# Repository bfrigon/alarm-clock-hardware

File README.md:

alarm-clock
===========

Project page at http://www.bfrigon.com/posts/projects/alarm-clock

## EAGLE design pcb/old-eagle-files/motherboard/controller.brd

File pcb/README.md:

Index
-----

Doc ID        | Part #            | Description
--------------|-------------------|-------------------------------------------------
CLK-DWG-01    | CLK-PC-01         | Led Matrix display board dimensions
CLK-DWG-02    | CLK-PC-02         | Touch keypad dimensions
CLK-DWG-03    | CLK-PC-03         | Motherboard dimensions
CLK-DWG-05    | CLK-PC-04         | Left panel PCB dimensions
CLK-DWG-08    | CLK-PC-05         | Display (model B) - Segments PCB
CLK-DWG-09    | CLK-PC-06         | Display (model B) - Dots PCB
CLK-DWG-10    | CLK-PC-07         | Display (model B) - Base PCB
CLK-DWG-12    | CLK-PC-08         | Battery interface PCB

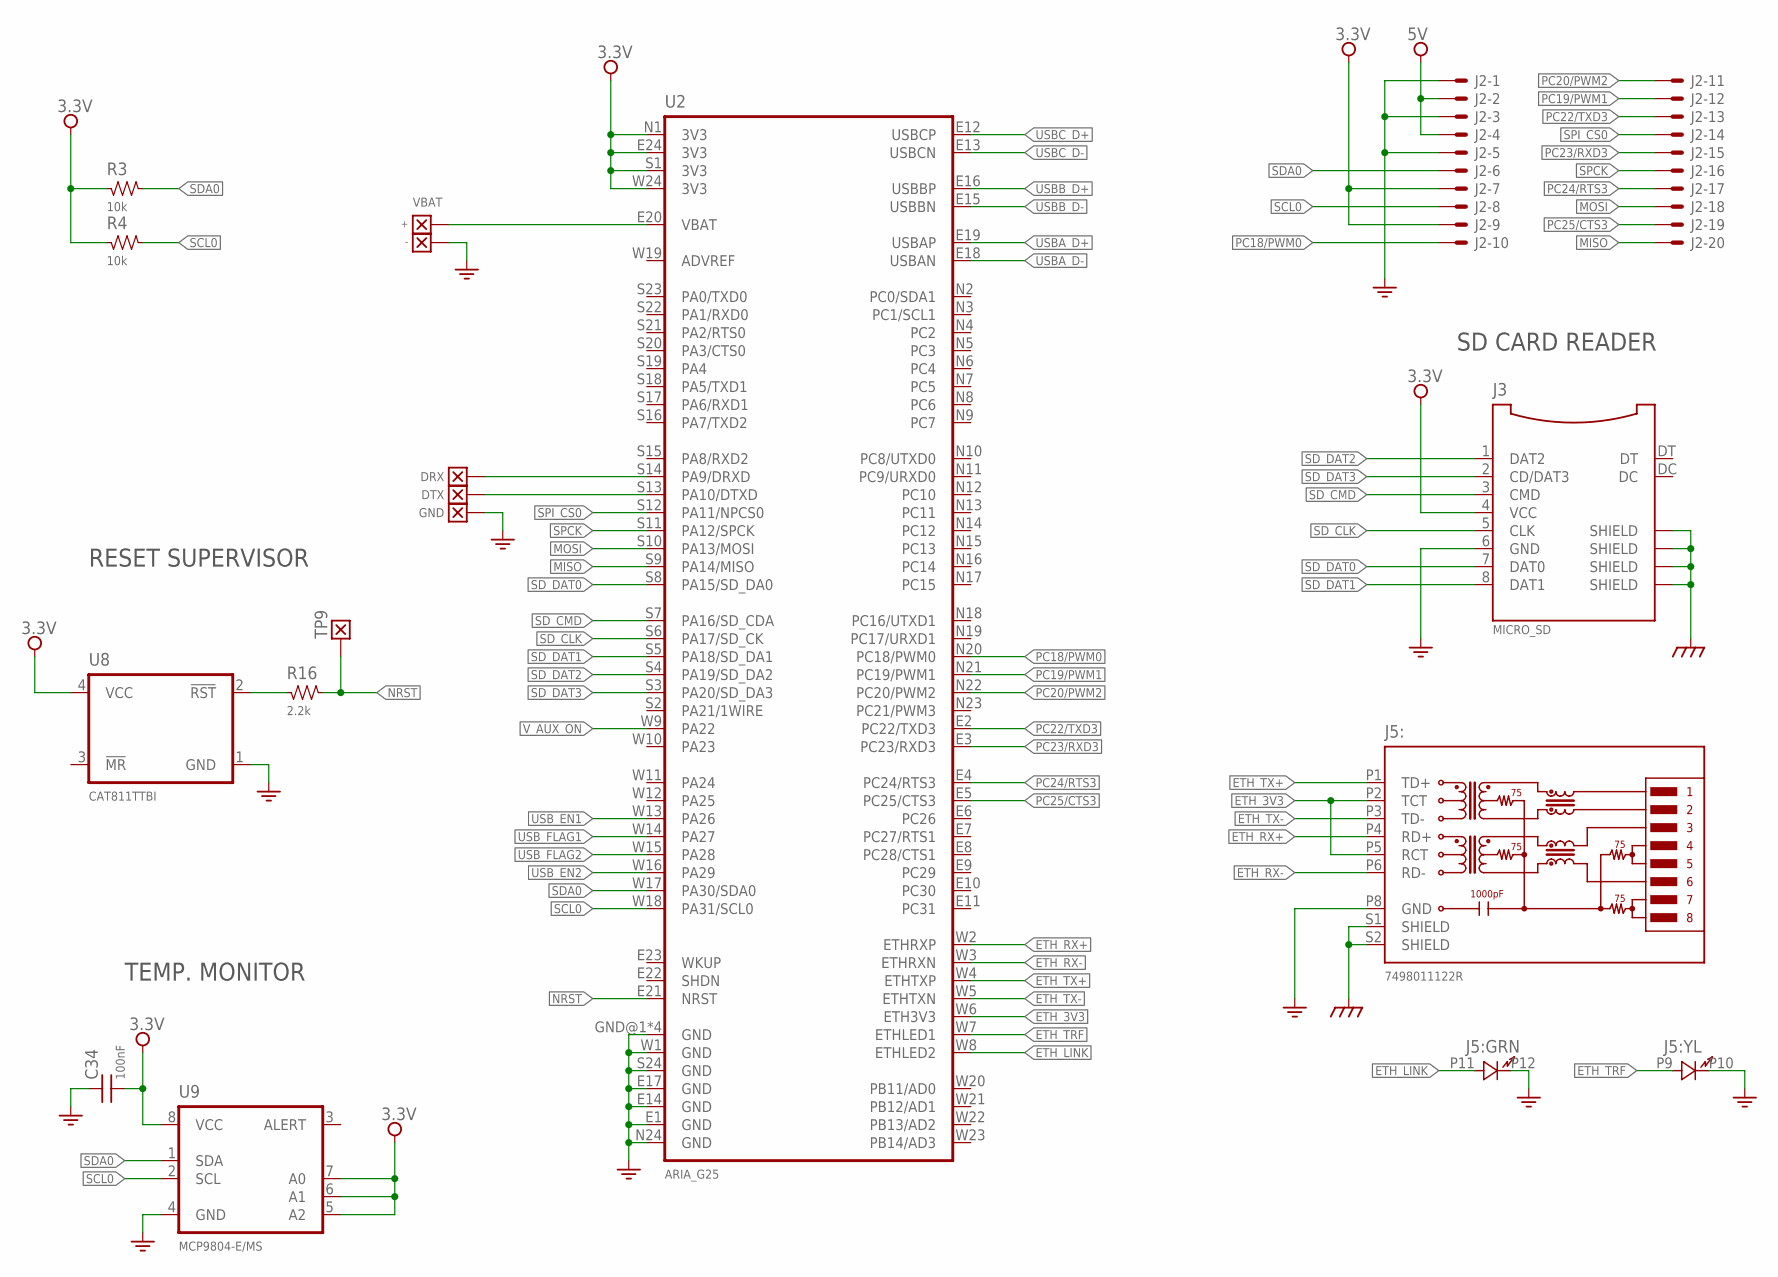
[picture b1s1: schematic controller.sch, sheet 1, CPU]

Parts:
C34: 100nF; SMD_0603
J2: DL-1.25MM-HEADER-20; DF13A-20DP-1.25
J3: MICRO_SD; 5027020891
J5: 7498011122R
R3, R4: 10k; SMD_0603
R16: 2.2k; SMD_0603
TP1: +; WIRE_SMT_150X75
TP2: -; WIRE_SMT_150X75
TP9: TEST_POINT-050; TP_050
U2: ARIA_G25
U8: CAT811TTBI; SOT143
U9: MCP9804-E/MS; MSOP8
W2: DRX; WIRE_SMT_150X75
W3: DTX; WIRE_SMT_150X75
W4: GND; WIRE_SMT_150X75

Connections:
3.3V: C34.2, J2.7, J2.9, J3.4 (VCC), R3.1, R4.1, U2.E24 (3V3), U2.N1 (3V3), U2.S1 (3V3), U2.W24 (3V3), U8.4 (VCC), U9.5 (A2), U9.6 (A1), U9.7 (A0), U9.8 (VCC); also elsewhere on the board
5V: J2.2, J2.4; also elsewhere on the board
DRX: U2.S14 (PA9/DRXD), W2.1
DTX: U2.S13 (PA10/DTXD), W3.1
EARTH: J3.SHDL@3 (SHIELD), J3.SHLD@1 (SHIELD), J3.SHLD@2 (SHIELD), J3.SHLD@4 (SHIELD), J5.S1 (SHIELD), J5.S2 (SHIELD); also elsewhere on the board
ETH_3V3: J5.P2 (TCT), J5.P5 (RCT), U2.W6 (ETH3V3)
ETH_LINK: J5.P11 (A), U2.W8 (ETHLED2)
ETH_RX+: J5.P4 (RD+), U2.W2 (ETHRXP)
ETH_RX-: J5.P6 (RD-), U2.W3 (ETHRXN)
ETH_TRF: J5.P9 (A), U2.W7 (ETHLED1)
ETH_TX+: J5.P1 (TD+), U2.W4 (ETHTXP)
ETH_TX-: J5.P3 (TD-), U2.W5 (ETHTXN)
GND: C34.1, J2.1, J2.3, J2.5, J3.6 (GND), J5.P8 (GND), J5.P10 (K), J5.P12 (K), TP2.1, U2.E1 (GND), U2.E14 (GND), U2.E17 (GND), U2.GND@1 (GND), U2.GND@2 (GND), U2.GND@3 (GND), U2.GND@4 (GND), U2.N24 (GND), U2.S24 (GND), U2.W1 (GND), U8.1 (GND), U9.4 (GND), W4.1; also elsewhere on the board
MISO: J2.20, U2.S9 (PA14/MISO)
MOSI: J2.18, U2.S10 (PA13/MOSI)
unnamed: TP1.1, U2.E20 (VBAT)
unnamed: R16.1, U8.2 (!RST)
NRST: R16.2, TP9.1, U2.E21 (NRST)
PC18/PWM0: J2.10, U2.N20 (PC18/PWM0)
PC19/PWM1: J2.12, U2.N21 (PC19/PWM1)
PC20/PWM2: J2.11, U2.N22 (PC20/PWM2)
PC22/TXD3: J2.13, U2.E2 (PC22/TXD3)
PC23/RXD3: J2.15, U2.E3 (PC23/RXD3)
PC24/RTS3: J2.17, U2.E4 (PC24/RTS3)
PC25/CTS3: J2.19, U2.E5 (PC25/CTS3)
SCL0: J2.8, R4.2, U2.W18 (PA31/SCL0), U9.2 (SCL); also elsewhere on the board
SDA0: J2.6, R3.2, U2.W17 (PA30/SDA0), U9.1 (SDA); also elsewhere on the board
SD_CLK: J3.5 (CLK), U2.S6 (PA17/SD_CK)
SD_CMD: J3.3 (CMD), U2.S7 (PA16/SD_CDA)
SD_DAT0: J3.7 (DAT0), U2.S8 (PA15/SD_DA0)
SD_DAT1: J3.8 (DAT1), U2.S5 (PA18/SD_DA1)
SD_DAT2: J3.1 (DAT2), U2.S4 (PA19/SD_DA2)
SD_DAT3: J3.2 (CD/DAT3), U2.S3 (PA20/SD_DA3)
SPCK: J2.16, U2.S11 (PA12/SPCK)
SPI_CS0: J2.14, U2.S12 (PA11/NPCS0)
USBA_D+: U2.E19 (USBAP); also elsewhere on the board
USBA_D-: U2.E18 (USBAN); also elsewhere on the board
USBB_D+: U2.E16 (USBBP); also elsewhere on the board
USBB_D-: U2.E15 (USBBN); also elsewhere on the board
USBC_D+: U2.E12 (USBCP); also elsewhere on the board
USBC_D-: U2.E13 (USBCN); also elsewhere on the board
USB_EN1: U2.W13 (PA26); also elsewhere on the board
USB_EN2: U2.W16 (PA29); also elsewhere on the board
USB_FLAG1: U2.W14 (PA27); also elsewhere on the board
USB_FLAG2: U2.W15 (PA28); also elsewhere on the board
V_AUX_ON: U2.W9 (PA22); also elsewhere on the board

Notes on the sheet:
VBAT
RESET SUPERVISOR
TEMP. MONITOR
SD CARD READER

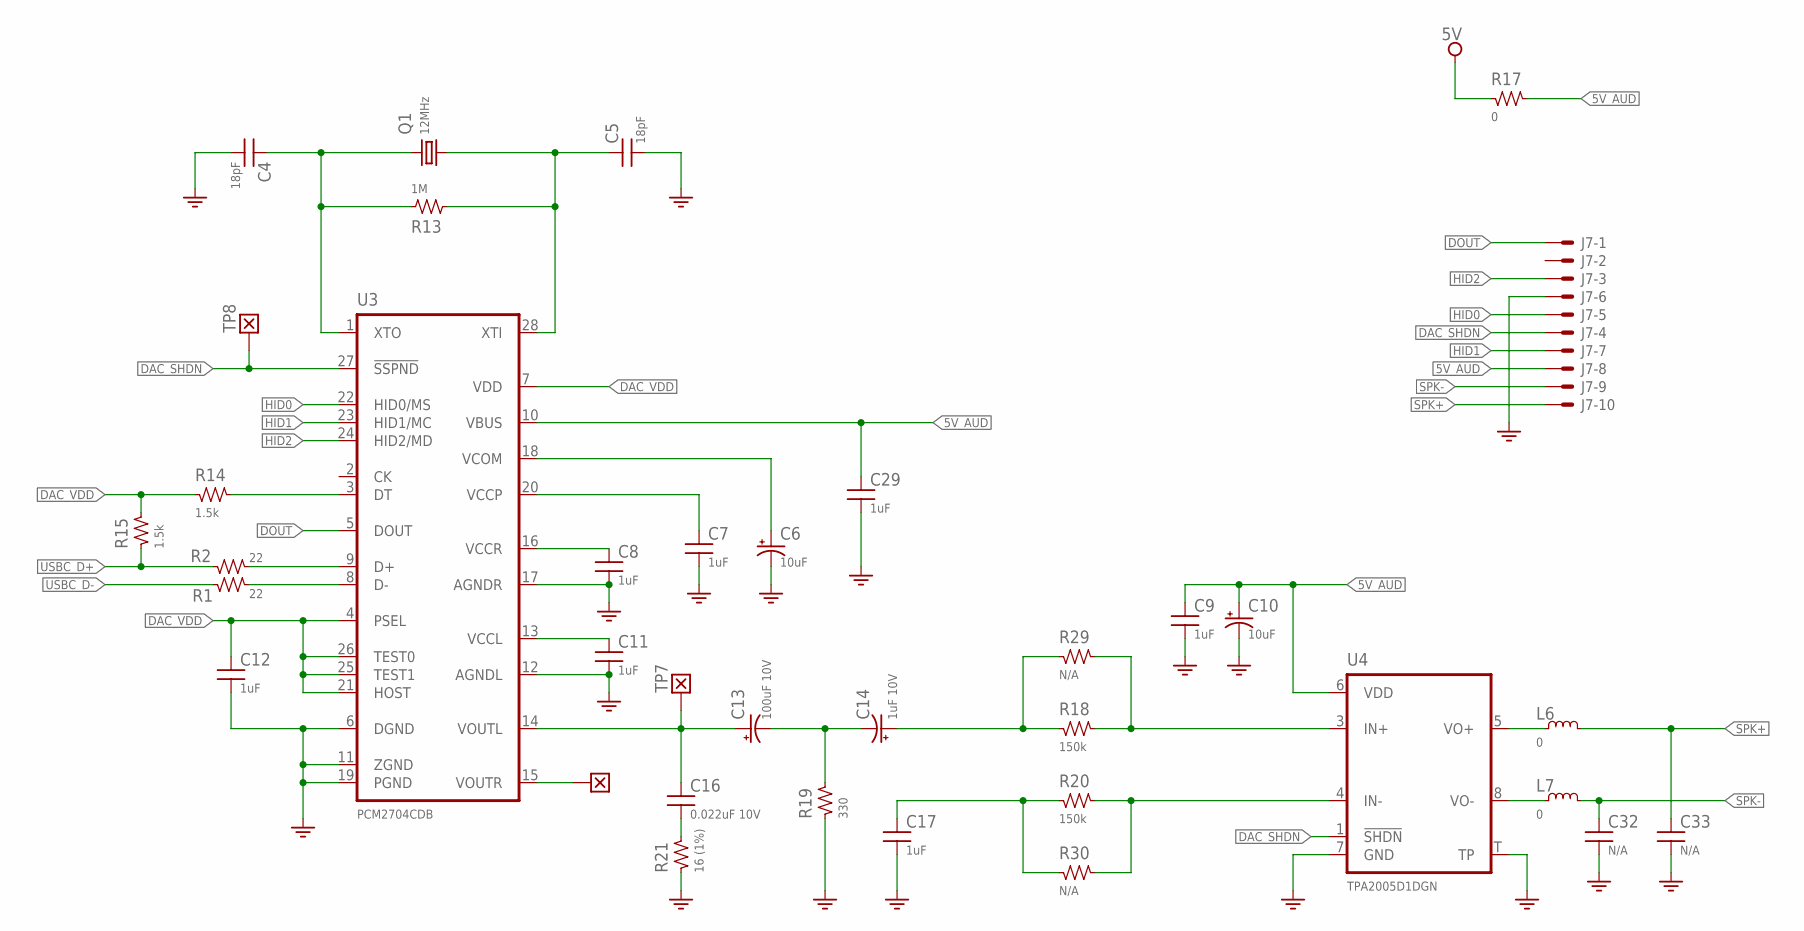
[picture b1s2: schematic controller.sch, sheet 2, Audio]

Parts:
C4, C5: 18pF; SMD_0603
C6, C10: 10uF; CAP_S0805
C7, C8, C9, C11, C12, C17, C29: 1uF; SMD_0603
C13: 100uF 10V; CAP_S1210
C14: 1uF 10V; CAP_S0805
C16: 0.022uF 10V; SMD_0603
C32, C33: N/A; SMD_0603
J7: DL-1.25MM-HEADER-10; DF13A-10DP-1.25
L6, L7: 0; SMD_0603
Q1: 12MHz; HC49UP
R1, R2: 22; SMD_0603
R13: 1M; SMD_0603
R14, R15: 1.5k; SMD_0603
R17: 0; SMD_1206
R18, R20: 150k; SMD_0603
R19: 330; SMD_0603
R21: 16 (1%); SMD_0603
R29, R30: N/A; SMD_0603
TP7, TP8: TEST_POINT-050; TP_050
U3: PCM2704CDB; SSOP28
U4: TPA2005D1DGN; PPSOP8
W1: WIRE-150X75; WIRE_SMT_150X75

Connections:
5V: R17.1; also elsewhere on the board
5V_AUD: C9.1, C10.+, C29.1, J7.8, R17.2, U3.10 (VBUS), U4.6 (VDD)
DAC_SHDN: J7.4, TP8.1, U3.27 (!SSPND), U4.1 (!SHDN)
DAC_VDD: C12.1, R14.1, R15.2, U3.4 (PSEL), U3.7 (VDD), U3.21 (HOST), U3.25 (TEST1), U3.26 (TEST0)
DOUT: J7.1, U3.5 (DOUT)
GND: C4.2, C5.2, C6.-, C7.2, C8.2, C9.2, C10.-, C11.2, C12.2, C17.2, C29.2, C32.2, C33.2, J7.6, R19.1, R21.1, U3.6 (DGND), U3.11 (ZGND), U3.12 (AGNDL), U3.17 (AGNDR), U3.19 (PGND), U4.7 (GND), U4.T (TP); also elsewhere on the board
HID0: J7.5, U3.22 (HID0/MS)
HID1: J7.7, U3.23 (HID1/MC)
HID2: J7.3, U3.24 (HID2/MD)
unnamed: R2.2, U3.9 (D+)
unnamed: R1.2, U3.8 (D-)
unnamed: C11.1, U3.13 (VCCL)
unnamed: C6.+, U3.18 (VCOM)
unnamed: C7.1, U3.20 (VCCP)
unnamed: C8.1, U3.16 (VCCR)
unnamed: C14.+, R18.1, R29.1
unnamed: R14.2, U3.3 (DT)
unnamed: U3.15 (VOUTR), W1.1
unnamed: L6.1, U4.5 (VO+)
unnamed: L7.1, U4.8 (VO-)
unnamed: R18.2, R29.2, U4.3 (IN+)
unnamed: R20.2, R30.2, U4.4 (IN-)
unnamed: C17.1, R20.1, R30.1
unnamed: C13.-, C14.-, R19.2
unnamed: C16.2, R21.2
SPK+: C33.1, J7.10, L6.2
SPK-: C32.1, J7.9, L7.2
USBC_D+: R2.1, R15.1; also elsewhere on the board
USBC_D-: R1.1; also elsewhere on the board
VOUTL: C13.+, C16.1, TP7.1, U3.14 (VOUTL)
XTI: C5.1, Q1.2, R13.2, U3.28 (XTI)
XTO: C4.1, Q1.1, R13.1, U3.1 (XTO)

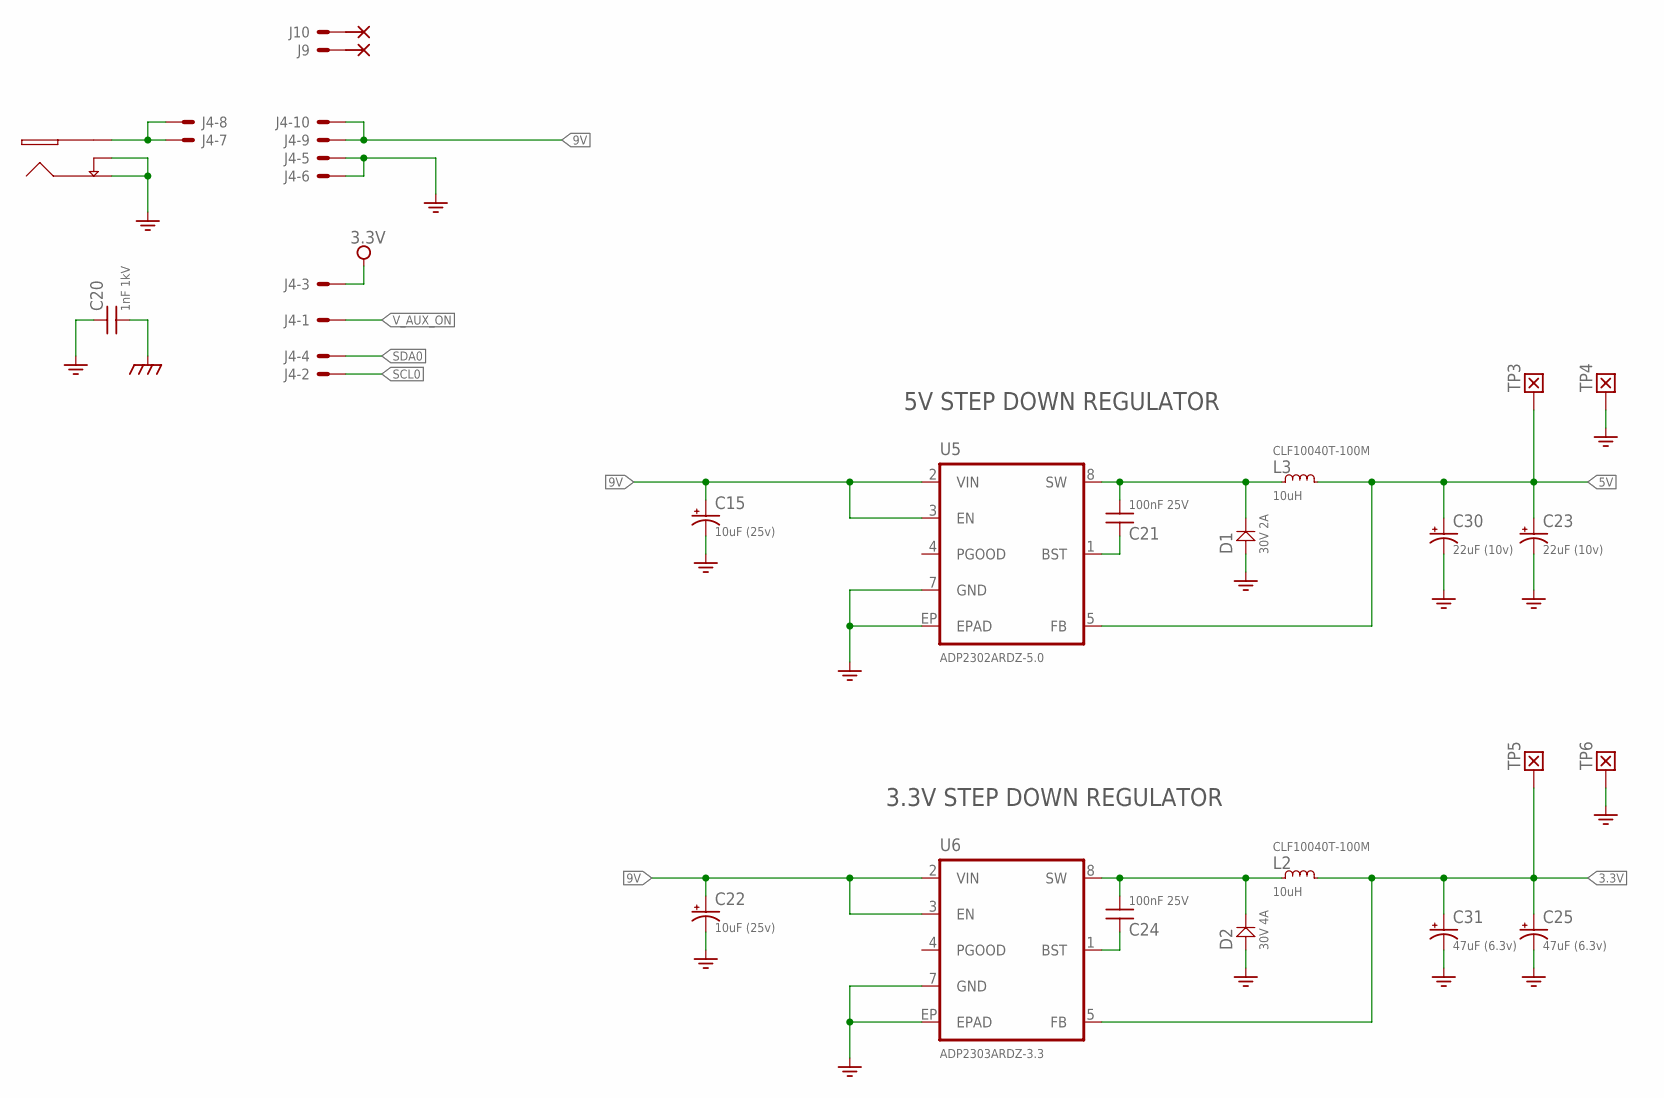
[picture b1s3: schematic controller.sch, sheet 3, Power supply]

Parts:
C15, C22: 10uF (25v); CAP_S1210; PART_NO TPSB106K025R1800
C20: 1nF 1kV; SMD_0805
C21, C24: 100nF 25V; SMD_0603
C23, C30: 22uF (10v); CAP_S1206; PART_NO TPSA226M010R0900
C25, C31: 47uF (6.3v); CAP_S1206; PART_NO TPSA476K006R0800
D1: 30V 2A; DIODE_DO214-AA
D2: 30V 4A; DIODE_DO214-AA
J4: DL-100-HEADER-10-V; 534206-5
J8: CUI-PJ-013C
J9, J10: SNG-100-HEADER-01-HDR-V; HDR_M_1
L2, L3: 10uH; IND-10X10; PART_NO CLF10040T-100M
TP3, TP4, TP5, TP6: TEST_POINT-050; TP_050
U5: ADP2302ARDZ-5.0; SOIC8-EP
U6: ADP2303ARDZ-3.3; SOIC8-EP

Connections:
3.3V: C25.+, C31.+, J4.3, L2.2, TP5.1, U6.5 (FB); also elsewhere on the board
5V: C23.+, C30.+, L3.2, TP3.1, U5.5 (FB); also elsewhere on the board
9V: C15.+, C22.+, J4.9, J4.10, U5.2 (VIN), U5.3 (EN), U6.2 (VIN), U6.3 (EN)
BST_3.3V: C24.1, U6.1 (BST)
BST_5V: C21.1, U5.1 (BST)
EARTH: C20.2; also elsewhere on the board
GND: C15.-, C20.1, C22.-, C23.-, C25.-, C30.-, C31.-, D1.A, D2.A, J4.5, J4.6, J8.2 (GND), J8.3 (SW), TP4.1, TP6.1, U5.7 (GND), U5.EP (EPAD), U6.7 (GND), U6.EP (EPAD); also elsewhere on the board
unnamed: J4.7, J4.8, J8.1 (V+)
SCL0: J4.2; also elsewhere on the board
SDA0: J4.4; also elsewhere on the board
SW_3.3: C24.2, D2.K, L2.1, U6.8 (SW)
SW_5V: C21.2, D1.K, L3.1, U5.8 (SW)
V_AUX_ON: J4.1; also elsewhere on the board

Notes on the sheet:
5V STEP DOWN REGULATOR
3.3V STEP DOWN REGULATOR

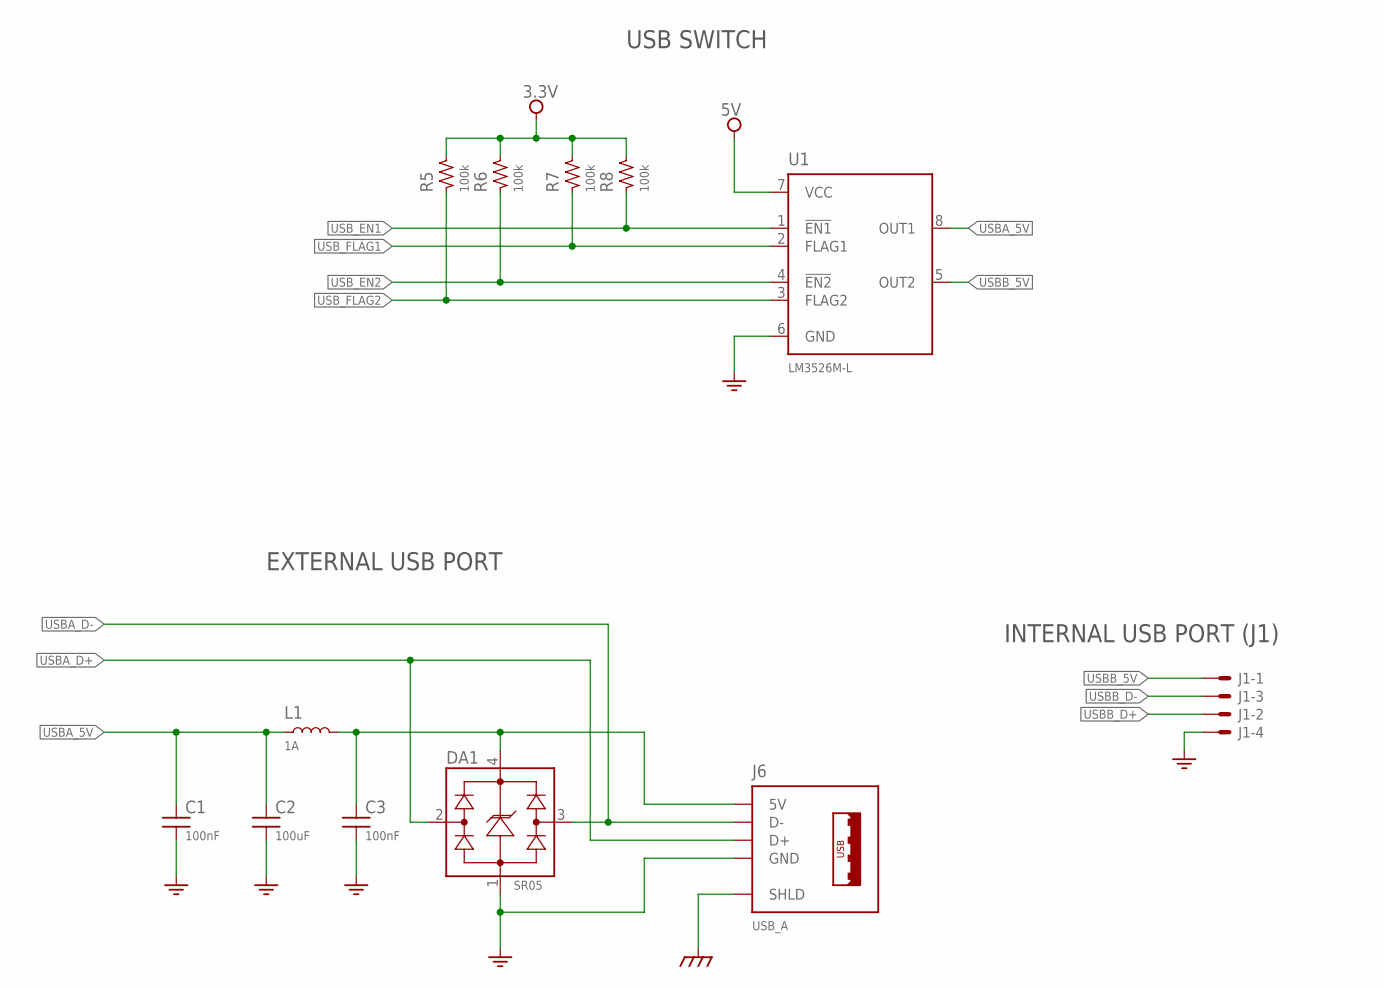
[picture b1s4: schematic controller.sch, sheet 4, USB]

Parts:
C1, C3: 100nF; SMD_0603
C2: 100uF; SMD_0805
DA1: SR05; SOT143
J1: SNG-2MM-HEADER-04-V; DF3X-4P-2DSA
J6: USB_A; 292303-1
L1: 1A; SMD_0805
R5, R6, R7, R8: 100k; SMD_0603
U1: LM3526M-L; SOIC8

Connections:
3.3V: R5.2, R6.2, R7.2, R8.2; also elsewhere on the board
5V: U1.7 (VCC); also elsewhere on the board
EARTH: J6.SHLD@1 (SHLD), J6.SHLD@2 (SHLD); also elsewhere on the board
GND: C1.2, C2.2, C3.2, DA1.1, J1.4, J6.4 (GND), U1.6 (GND); also elsewhere on the board
unnamed: C3.1, DA1.4, J6.1 (5V), L1.2
USBA_5V: C1.1, C2.1, L1.1, U1.8 (OUT1)
USBA_D+: DA1.2, J6.3 (D+); also elsewhere on the board
USBA_D-: DA1.3, J6.2 (D-); also elsewhere on the board
USBB_5V: J1.1, U1.5 (OUT2)
USBB_D+: J1.2; also elsewhere on the board
USBB_D-: J1.3; also elsewhere on the board
USB_EN1: R8.1, U1.1 (!EN1); also elsewhere on the board
USB_EN2: R6.1, U1.4 (!EN2); also elsewhere on the board
USB_FLAG1: R7.1, U1.2 (FLAG1); also elsewhere on the board
USB_FLAG2: R5.1, U1.3 (FLAG2); also elsewhere on the board

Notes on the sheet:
USB SWITCH
EXTERNAL USB PORT
INTERNAL USB PORT (J1)

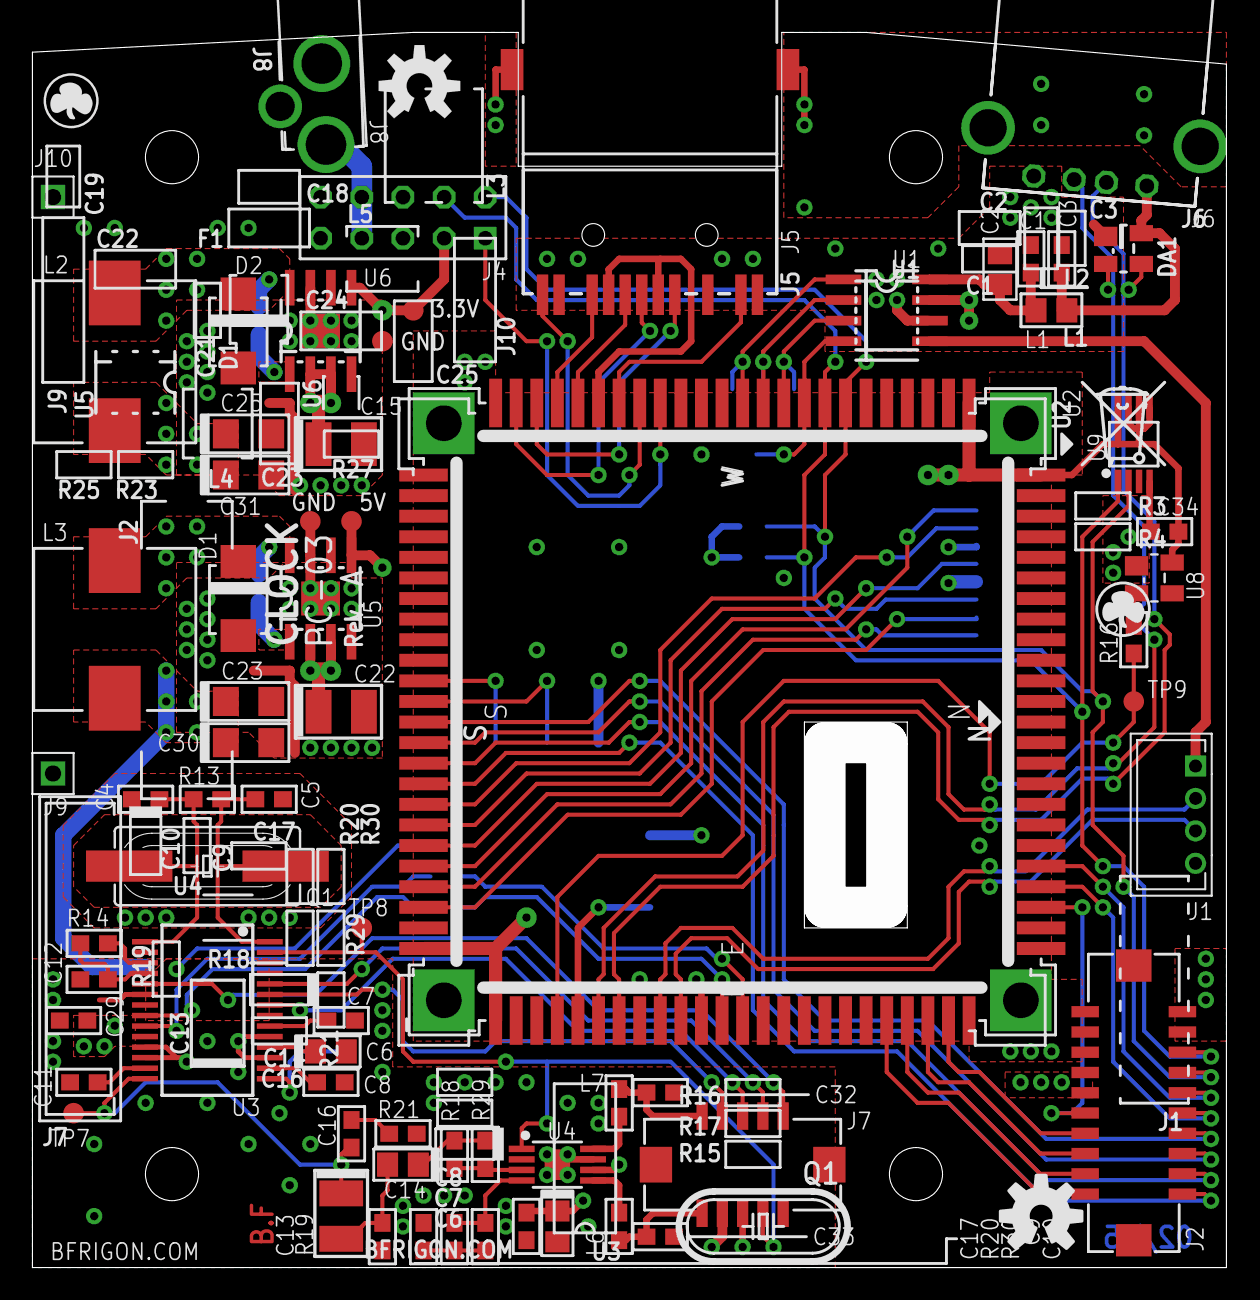
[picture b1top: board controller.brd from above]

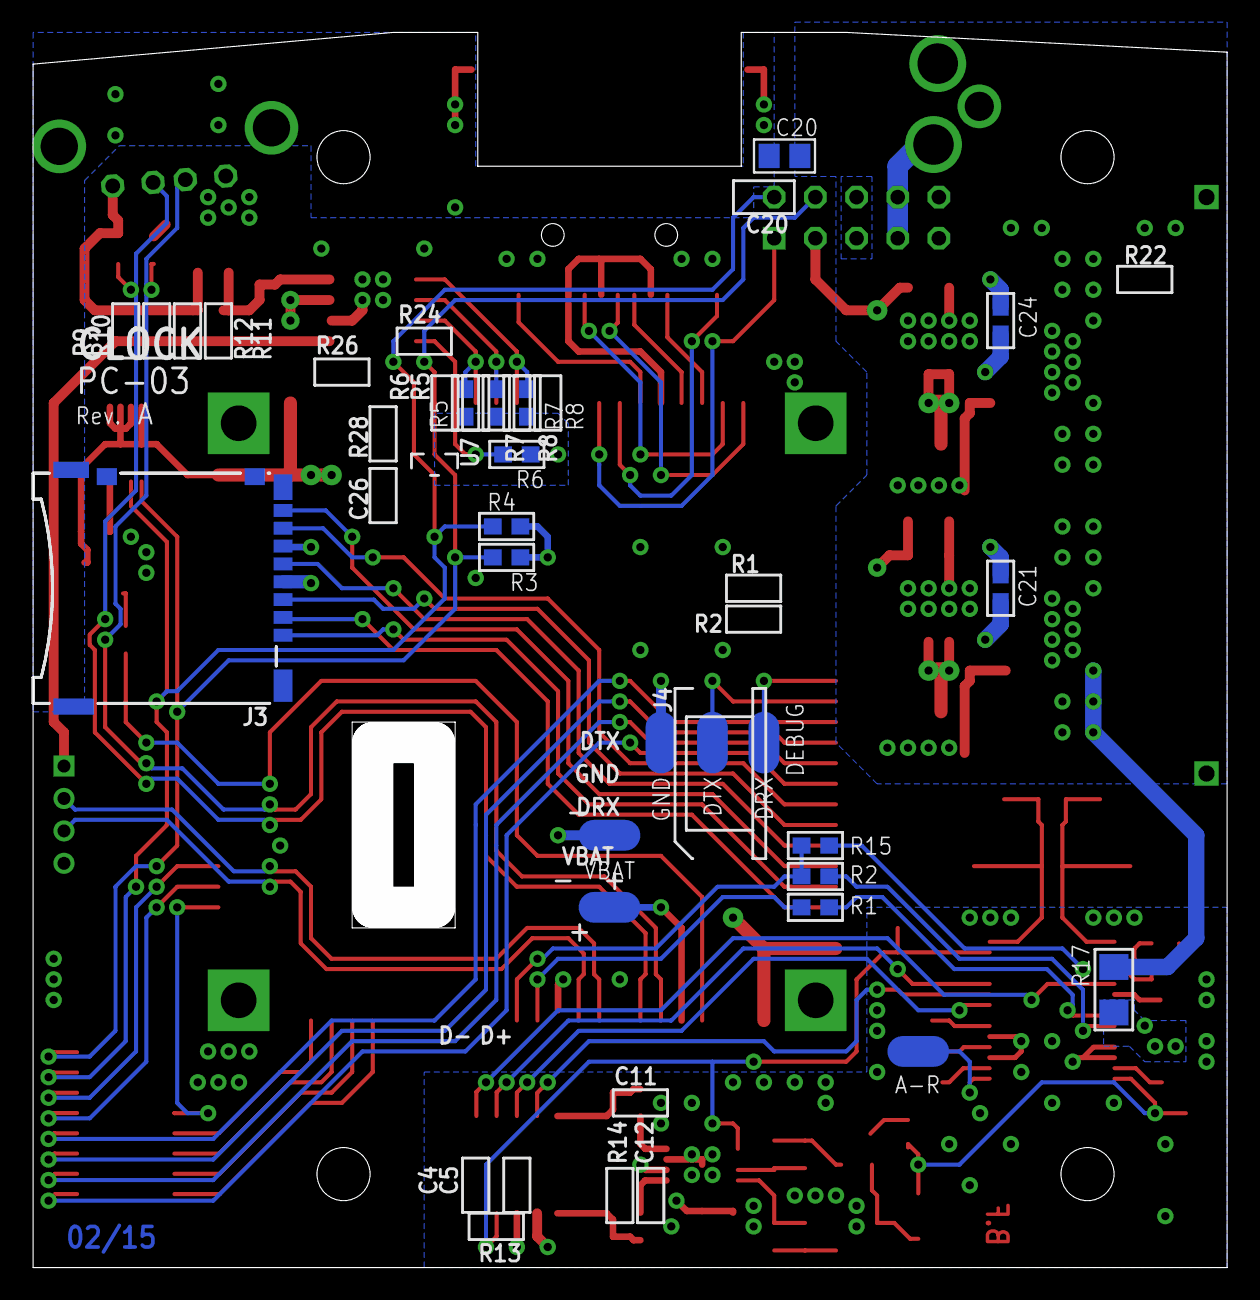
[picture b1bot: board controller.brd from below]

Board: 4 copper layers, 73.7 x 76.2 mm, 93 parts (22 on the bottom side), 83 nets.

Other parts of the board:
U$1: OPENHW_LOGO_200
U$2: INFO_DATE
U$3: INFO_COMPACT
U$4: LOGO2
U$6: INFO_AUTHOR

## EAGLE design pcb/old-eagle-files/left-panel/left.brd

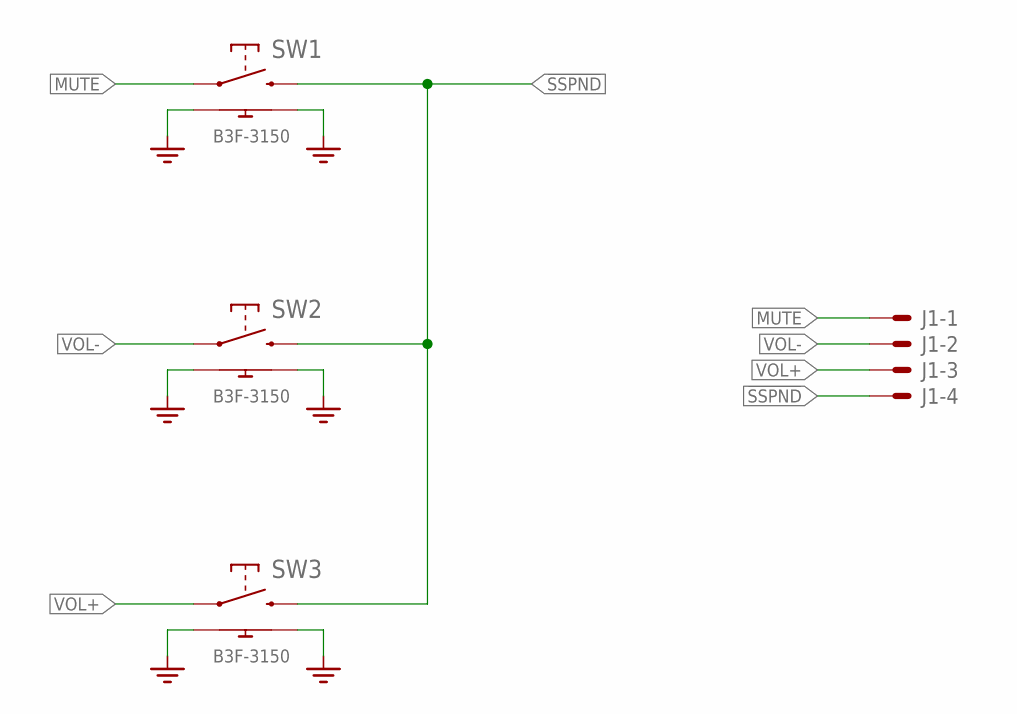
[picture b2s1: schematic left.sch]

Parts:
J1: SNG-2MM-HEADER-04-V; DF3X-4P-2DSA
SW1, SW2, SW3: B3F-3150; B3F-315X

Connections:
!SSPND: J1.4, SW1.2, SW2.2, SW3.2
GND: SW1.3, SW1.4, SW2.3, SW2.4, SW3.3, SW3.4
MUTE: J1.1, SW1.1
VOL+: J1.3, SW3.1
VOL-: J1.2, SW2.1

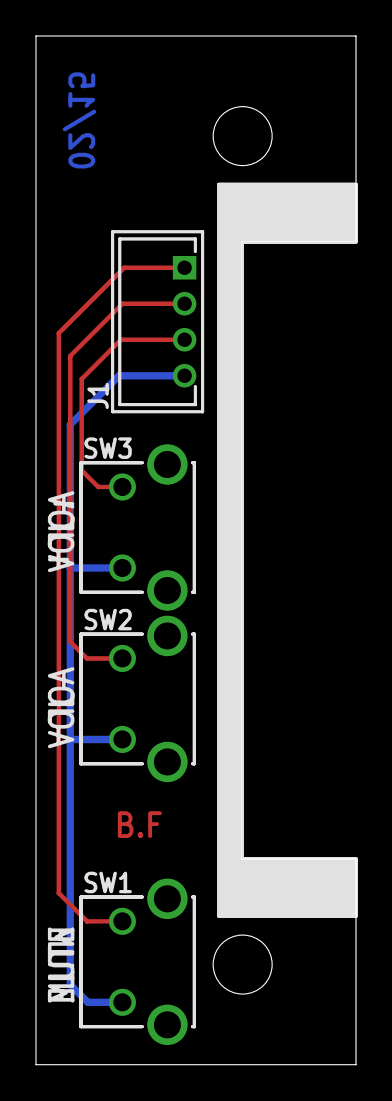
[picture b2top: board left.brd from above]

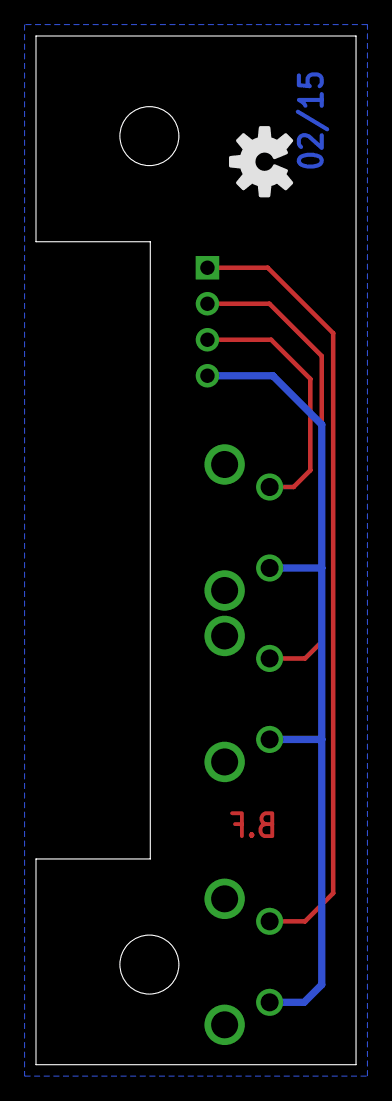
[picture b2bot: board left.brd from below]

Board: 2 copper layers, 17.8 x 57.1 mm, 7 parts (2 on the bottom side), 5 nets.

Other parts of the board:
U$1: INFO_AUTHOR
U$2: INFO_DATE
U$3: OPENHW_LOGO_150

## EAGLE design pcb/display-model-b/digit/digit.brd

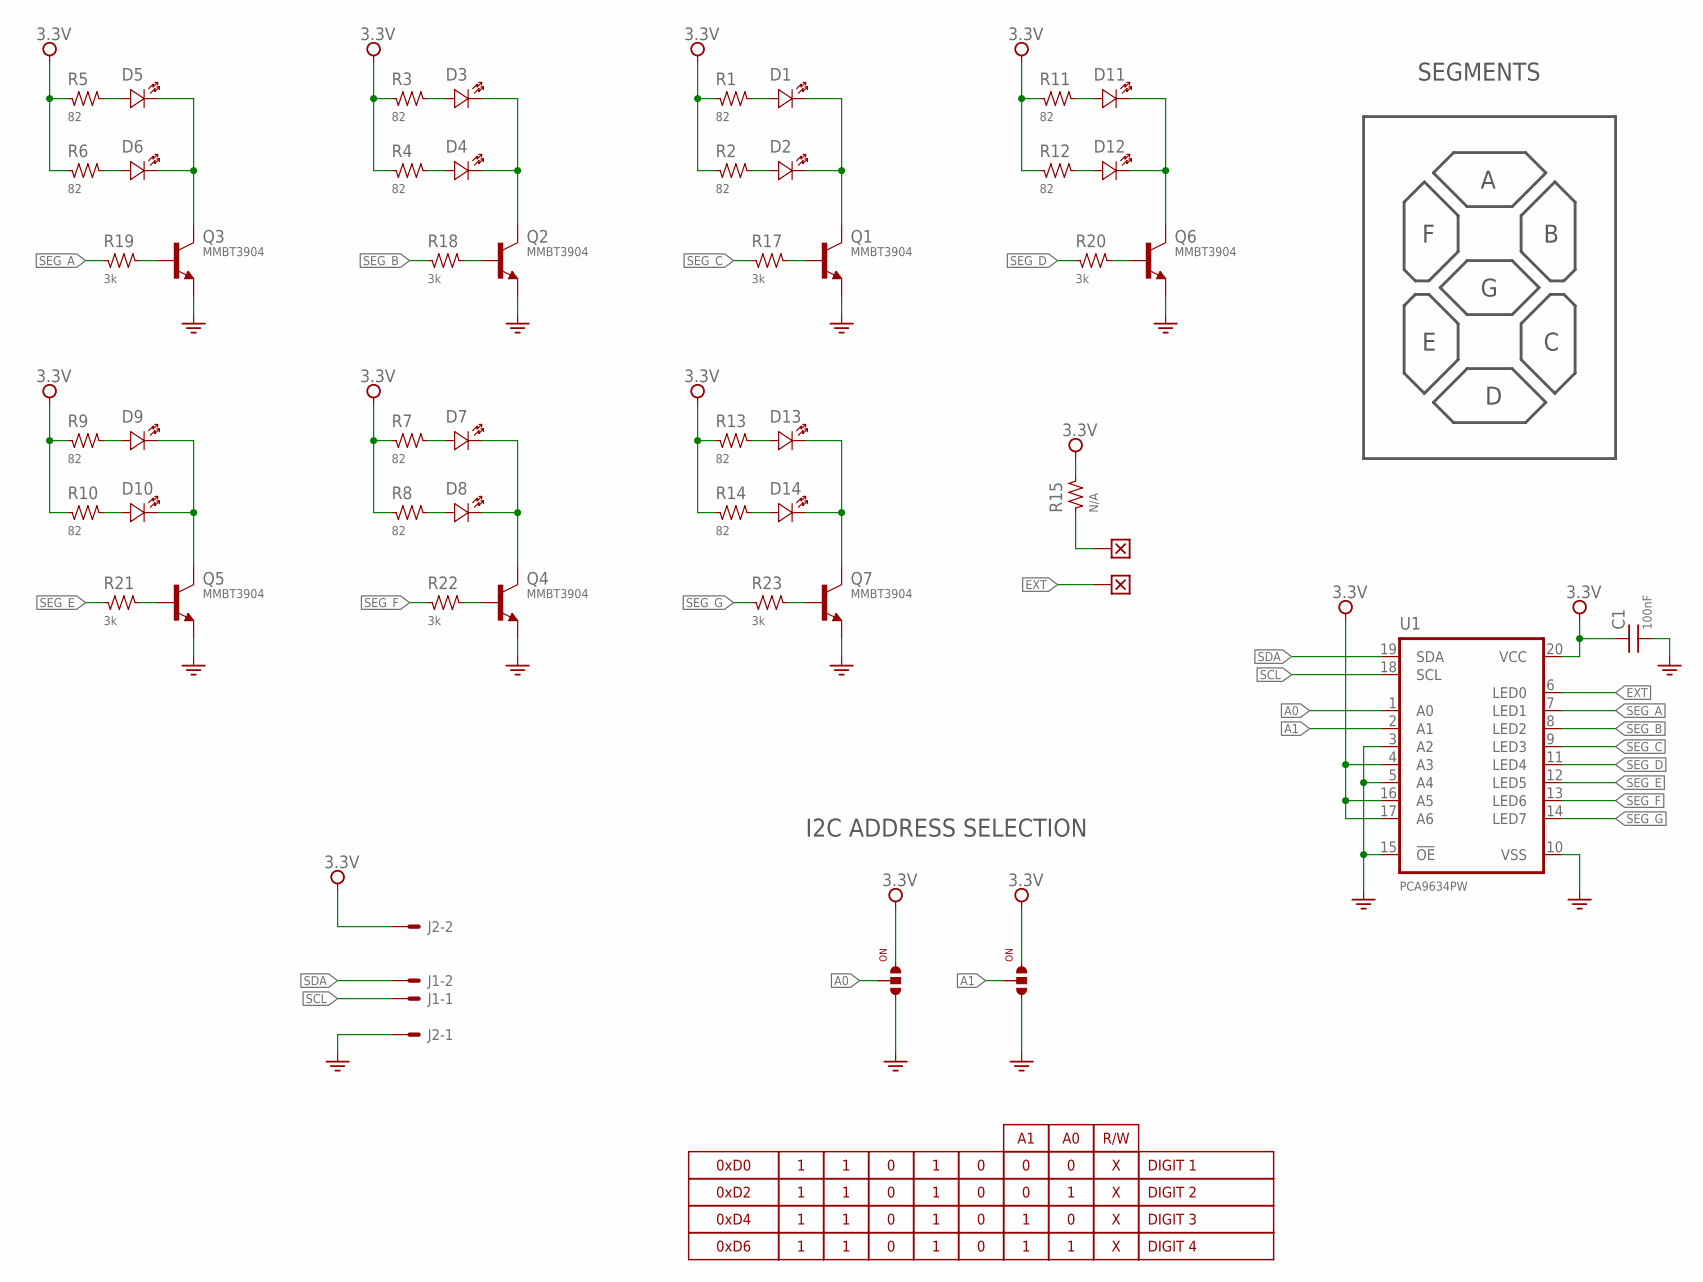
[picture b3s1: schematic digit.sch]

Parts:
C1: 100nF; SMD_0603
D1, D2, D3, D4, D7, D8, D9, D10, D11, D12, D13, D14: Orange; CHIPLED_0805; PART_NO APT2012SECK/J4-PRV
D5: Red; CHIPLED_0805; PART_NO APT2012SECK/J4-PRV
D6: orange; CHIPLED_0805; PART_NO APT2012SECK/J4-PRV
J1, J2: DL-100-HEADER-02-EDGE; HDR100-EDGE-2; PART_NO 3-644456-2
J10, J11: SOLDER_JUMPER_3
Q1, Q2, Q3, Q4, Q5, Q6, Q7: MMBT3904; SOT23
R1, R2, R3, R4, R5, R6, R7, R8, R9, R10, R11, R12, R13, R14: 82; SMD_0603
R15: N/A; SMD_0603
R17, R18, R19, R20, R21, R22, R23: 3k; SMD_0603
U1: PCA9634PW; TSSOP20
W5, W6: WIRE; WIRE_SMT

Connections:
3.3V: C1.1, J2.2, J10.1, J11.1, R1.1, R2.1, R3.1, R4.1, R5.1, R6.1, R7.1, R8.1, R9.1, R10.1, R11.1, R12.1, R13.1, R14.1, R15.2, U1.4 (A3), U1.16 (A5), U1.17 (A6), U1.20 (VCC)
A0: J10.2, U1.1 (A0)
A1: J11.2, U1.2 (A1)
EXT: U1.6 (LED0), W5.1
GND: C1.2, J2.1, J10.3, J11.3, Q1.2 (E), Q2.2 (E), Q3.2 (E), Q4.2 (E), Q5.2 (E), Q6.2 (E), Q7.2 (E), U1.3 (A2), U1.5 (A4), U1.10 (VSS), U1.15 (!OE)
unnamed: Q1.1 (B), R17.2
unnamed: D7.K, D8.K, Q4.3 (C)
unnamed: D13.K, D14.K, Q7.3 (C)
unnamed: D1.K, D2.K, Q1.3 (C)
unnamed: D3.K, D4.K, Q2.3 (C)
unnamed: D5.K, D6.K, Q3.3 (C)
unnamed: D3.A, R3.2
unnamed: D4.A, R4.2
unnamed: D14.A, R14.2
unnamed: D13.A, R13.2
unnamed: D2.A, R2.2
unnamed: D1.A, R1.2
unnamed: D5.A, R5.2
unnamed: D6.A, R6.2
unnamed: D11.A, R11.2
unnamed: D9.K, D10.K, Q5.3 (C)
unnamed: D11.K, D12.K, Q6.3 (C)
unnamed: D12.A, R12.2
unnamed: D10.A, R10.2
unnamed: D9.A, R9.2
unnamed: D7.A, R7.2
unnamed: D8.A, R8.2
unnamed: Q2.1 (B), R18.2
unnamed: Q3.1 (B), R19.2
unnamed: Q6.1 (B), R20.2
unnamed: Q5.1 (B), R21.2
unnamed: Q4.1 (B), R22.2
unnamed: Q7.1 (B), R23.2
unnamed: R15.1, W6.1
SCL: J1.1, U1.18 (SCL)
SDA: J1.2, U1.19 (SDA)
SEG_A: R19.1, U1.7 (LED1)
SEG_B: R18.1, U1.8 (LED2)
SEG_C: R17.1, U1.9 (LED3)
SEG_D: R20.1, U1.11 (LED4)
SEG_E: R21.1, U1.12 (LED5)
SEG_F: R22.1, U1.13 (LED6)
SEG_G: R23.1, U1.14 (LED7)

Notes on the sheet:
I2C ADDRESS SELECTION
SEGMENTS

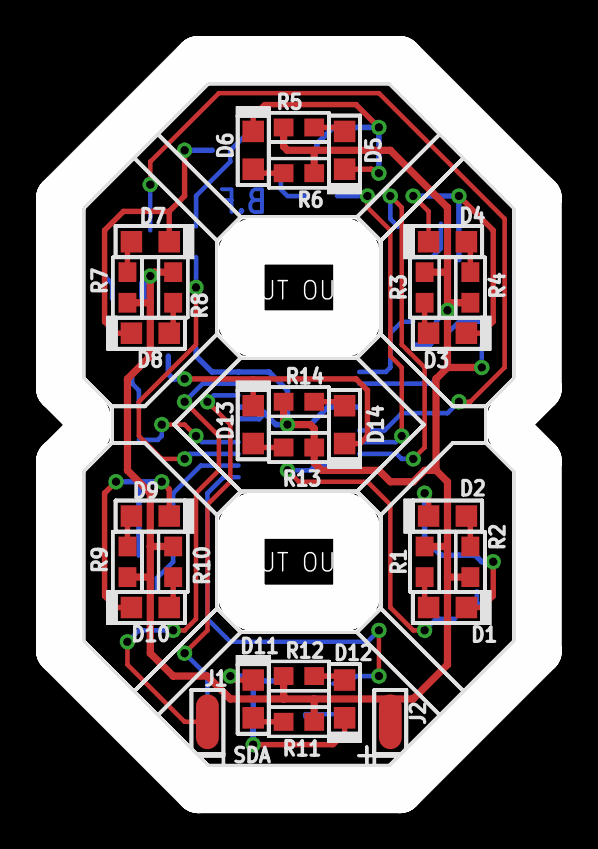
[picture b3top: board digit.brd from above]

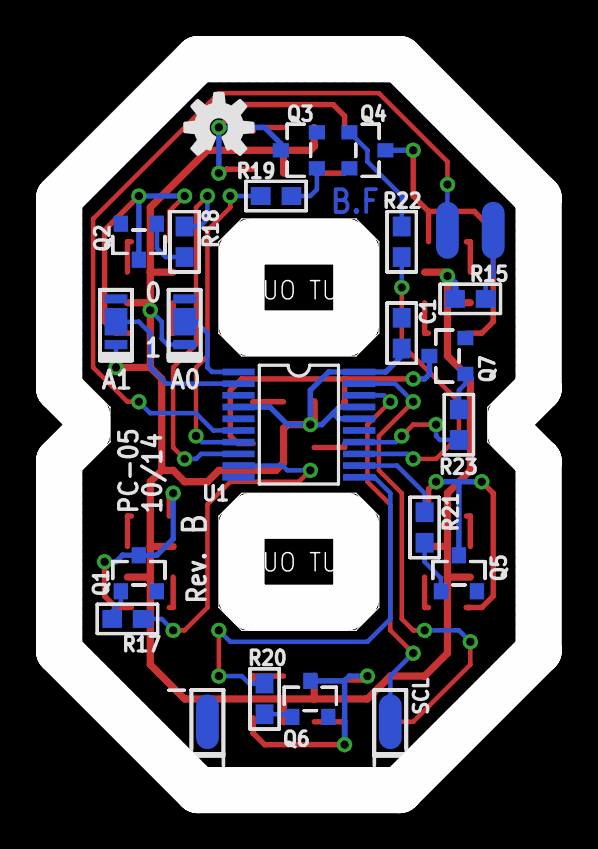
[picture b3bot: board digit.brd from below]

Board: 2 copper layers, 26.7 x 40.6 mm, 54 parts (24 on the bottom side), 43 nets.

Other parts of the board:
U$1: OPENHW_LOGO_150
U$2: INFO_AUTHOR
U$3: INFO_REV

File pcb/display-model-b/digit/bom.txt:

**********************************************************************************
*                                BILL OF MATERIAL                                *
**********************************************************************************

Last mod. : 2014-12-29 01:43:11
Doc. ID   : CLK-SCH-05
Project   : Alarm Clock (Model B)
Title     : 7 Segment display
             
Part #    : CLK-PC-05
REV.      : B


Qty | Names              | Description                    | Mfg. SKU        | Package      | Value     
=======================================================================================================
  2 | J1-J2              | 2 Pos - Dual Row - 2.54mm      | 3-644456-2      | HDR100-EDGE- | --        
    |                    |                                |                 | 2            |           
----|--------------------|--------------------------------|-----------------|--------------|-----------
 14 | D1-D14             | Led Chip 0805 - Orange         | APT2012SECK/J4- | SMT 0805     | Orange    
    |                    |                                | PRV             |              |           
----|--------------------|--------------------------------|-----------------|--------------|-----------
  1 | C1                 | Capacitor - SMT 0603 - 100nF   | CAP-0603        | SMT 0603     | 100nF     
----|--------------------|--------------------------------|-----------------|--------------|-----------
  7 | Q1-Q7              | NPN Transistor                 | MMBT3904        | SOT23        | --        
----|--------------------|--------------------------------|-----------------|--------------|-----------
  1 | U1                 | 8-bit fm+ i2c-bus LED driver   | PCA9634PW       | TSSOP20      | --        
----|--------------------|--------------------------------|-----------------|--------------|-----------
  7 | R17-R23            | Resistor - SMT 0603 - 3k       | RES-0603        | SMT 0603     | 3k        
----|--------------------|--------------------------------|-----------------|--------------|-----------
 14 | R1-R14             | Resistor - SMT 0603 - 82       | RES-0603        | SMT 0603     | 82        
----|--------------------|--------------------------------|-----------------|--------------|-----------
